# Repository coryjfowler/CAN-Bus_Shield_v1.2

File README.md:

CAN-Bus_Shield_v1.2
====================

I updated the schematic to migrate the SPI connections over to the ICSP header to allow the Shield to be compatible with other Arduinos that do not use digital pins 11-13 for SPI.  I also provided the option to select /INT pin.

This version is capable of operating at 3.3V BUT the MCP2562 still needs +5V to operate the CAN bus.  There is a solder-jumper pad to select the voltage of operation if IOREF pin is not used.

This version has two pinouts on the DE9 for CAN.  These two pinouts are not enabled by default, there are three solder-jumpers on the bottom of the PCB.  The dots indicate the "Standard CAN Pinout" commonly used and the opposite retains compatibility with the OBDII cable which started this whole mess.

This version features a split termination that is not enabled by default.  The split termination improves CMRR.

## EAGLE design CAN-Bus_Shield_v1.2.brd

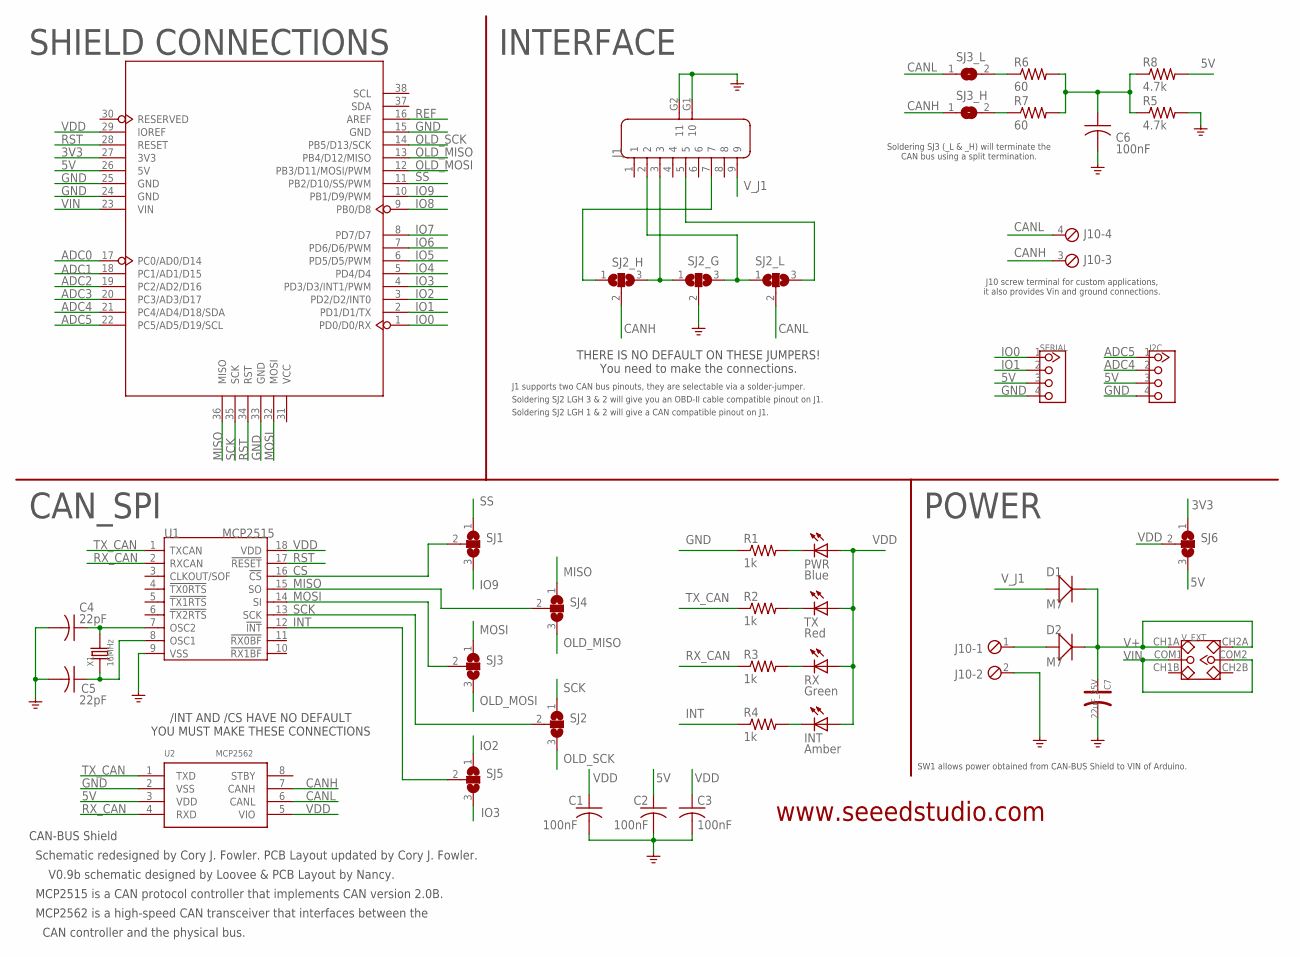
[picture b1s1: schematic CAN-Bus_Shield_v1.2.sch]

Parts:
C1, C2, C3: 100nF; C0603K
C4, C5: 22pF; C0603
C6: 100nF; C1210
C7: 22uF_25V; AVX-C
D1, D2: M7; D2010
I2C: TWIG-4P-2.0-2.0; 4P-2.0
INT: Amber; CHIP-LED0805
J1: DB9'MEAL'; DB9-MEAL
J10: MPT4; 4POL254
PWR: Blue; CHIP-LED0805
R1, R2, R3, R4: 1k; M0805
R5, R8: 4.7k; M3216
R6, R7: 60; M3216
RX: Green; CHIP-LED0805
SERIAL: TWIG-4P-2.0-2.0; 4P-2.0
SJ1, SJ2, SJ2_G, SJ2_H, SJ2_L, SJ3, SJ4, SJ5, SJ6: SJ2W; SJ_2
SJ3_H, SJ3_L: SJ
TX: Red; CHIP-LED0805
U1: MCP2515; SOIC18
U2: MCP2562; SO08
U3: ARDUINO
V_EXT: SWITCH-2CH-6P; 6P-2CH-2.54-7.6X3.0
X1: 16MHz; HC49/S

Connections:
3V3: SJ6.1, U3.27 (3V3)
5V: C2.1, I2C.3, R8.2, SERIAL.3, SJ6.3, U2.3 (VDD), U3.26 (5V)
ADC0: U3.17 (PC0/AD0/D14)
ADC1: U3.18 (PC1/AD1/D15)
ADC2: U3.19 (PC2/AD2/D16)
ADC3: U3.20 (PC3/AD3/D17)
ADC4: I2C.2, U3.21 (PC4/AD4/D18/SDA)
ADC5: I2C.1, U3.22 (PC5/AD5/D19/SCL)
CANH: J10.3, SJ2_H.2, SJ3_H.1, U2.7 (CANH)
CANL: J10.4, SJ2_L.2, SJ3_L.1, U2.6 (CANL)
CS: SJ1.2, U1.16 (!CS)
GND: C1.2, C2.2, C3.2, C4.2, C5.2, C6.2, C7.-, I2C.4, J1.G1 (10), J1.G2 (11), J10.2, R1.1, R5.2, SERIAL.4, SJ2_G.2, U1.9 (VSS), U2.2 (VSS), U3.15 (GND), U3.24 (GND), U3.25 (GND), U3.33 (GND)
INT: R4.1, SJ5.2, U1.12 (!INT)
IO0: SERIAL.1, U3.1 (PD0/D0/RX)
IO1: SERIAL.2, U3.2 (PD1/D1/TX)
IO2: SJ5.1, U3.3 (PD2/D2/INT0)
IO3: SJ5.3, U3.4 (PD3/D3/INT1/PWM)
IO4: U3.5 (PD4/D4)
IO5: U3.6 (PD5/D5/PWM)
IO6: U3.7 (PD6/D6/PWM)
IO7: U3.8 (PD7/D7)
IO8: U3.9 (PB0/D8)
IO9: SJ1.3, U3.10 (PB1/D9/PWM)
MISO: SJ4.1, SJ4.2, U1.15 (SO), U3.36 (MISO)
MOSI: SJ3.1, SJ3.2, U1.14 (SI), U3.32 (MOSI)
unnamed: PWR.C, R1.2
unnamed: R2.2, TX.C
unnamed: R3.2, RX.C
unnamed: J1.2, SJ2_G.3, SJ2_L.1
unnamed: J1.7, SJ2_H.1
unnamed: J1.3, SJ2_G.1, SJ2_H.3
unnamed: R6.1, SJ3_L.2
unnamed: R7.1, SJ3_H.2
unnamed: C6.1, R5.1, R6.2, R7.2, R8.1
unnamed: C5.1, U1.8 (OSC1), X1.1
unnamed: C4.1, U1.7 (OSC2), X1.2
unnamed: INT.C, R4.2
unnamed: J1.5, SJ2_L.3
OLD_MISO: SJ4.3, U3.13 (PB4/D12/MISO)
OLD_MOSI: SJ3.3, U3.12 (PB3/D11/MOSI/PWM)
OLD_SCK: SJ2.3, U3.14 (PB5/D13/SCK)
REF: U3.16 (AREF)
RST: U1.17 (!RESET), U3.28 (RESET), U3.34 (RST)
RX_CAN: R3.1, U1.2 (RXCAN), U2.4 (RXD)
SCK: SJ2.1, SJ2.2, U1.13 (SCK), U3.35 (SCK)
SS: SJ1.1, U3.11 (PB2/D10/SS/PWM)
TX_CAN: R2.1, U1.1 (TXCAN), U2.1 (TXD)
V+: C7.+, D1.-, D2.-, V_EXT.CH1A, V_EXT.CH2A
VDD: C1.1, C3.1, INT.A, PWR.A, RX.A, SJ6.2, TX.A, U1.18 (VDD), U2.5 (VIO), U3.29 (IOREF)
VIN: U3.23 (VIN), V_EXT.COM1, V_EXT.COM2
V_J1: D1.+, J1.9
V_J10: D2.+, J10.1

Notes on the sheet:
CAN_SPI
SHIELD CONNECTIONS
INTERFACE
POWER
CAN-BUS Shield
V0.9b schematic designed by Loovee & PCB Layout by Nancy.
Schematic redesigned by Cory J. Fowler. PCB Layout updated by Cory J. Fowler.
MCP2562 is a high-speed CAN transceiver that interfaces between the
CAN controller and the physical bus.
MCP2515 is a CAN protocol controller that implements CAN version 2.0B.
www.seeedstudio.com
SW1 allows power obtained from CAN-BUS Shield to VIN of Arduino.
J1 supports two CAN bus pinouts, they are selectable via a solder-jumper.
J10 screw terminal for custom applications, it also provides Vin and ground connections.
Soldering SJ2 LGH 3 & 2 will give you an OBD-II cable compatible pinout on J1.
Soldering SJ2 LGH 1 & 2 will give a CAN compatible pinout on J1.
Soldering SJ3 (_L & _H) will terminate the CAN bus using a split termination.
THERE IS NO DEFAULT ON THESE JUMPERS! You need to make the connections.
/INT AND /CS HAVE NO DEFAULT YOU MUST MAKE THESE CONNECTIONS

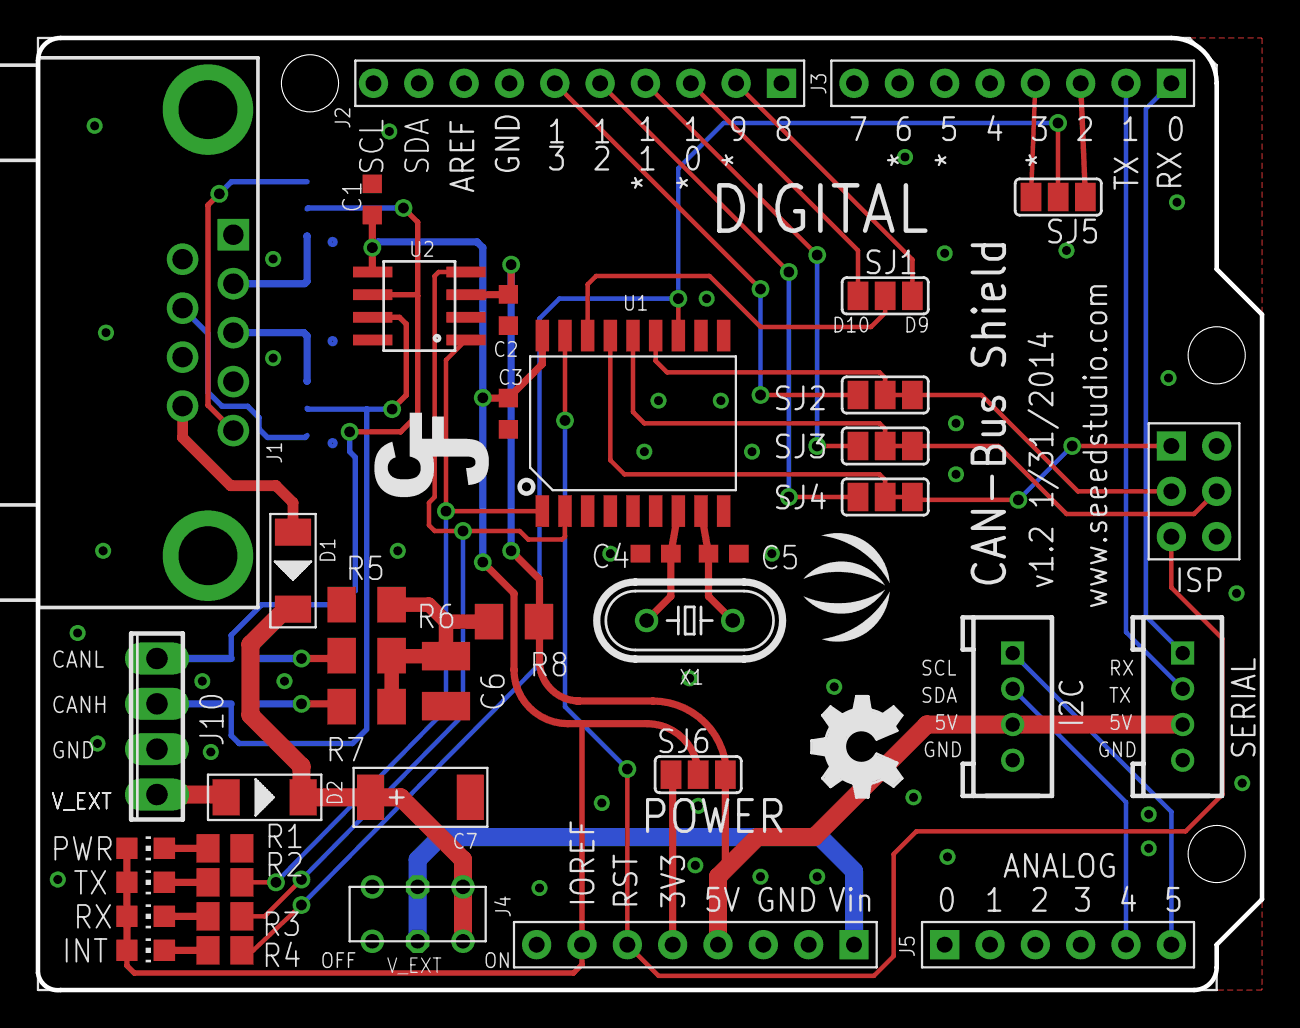
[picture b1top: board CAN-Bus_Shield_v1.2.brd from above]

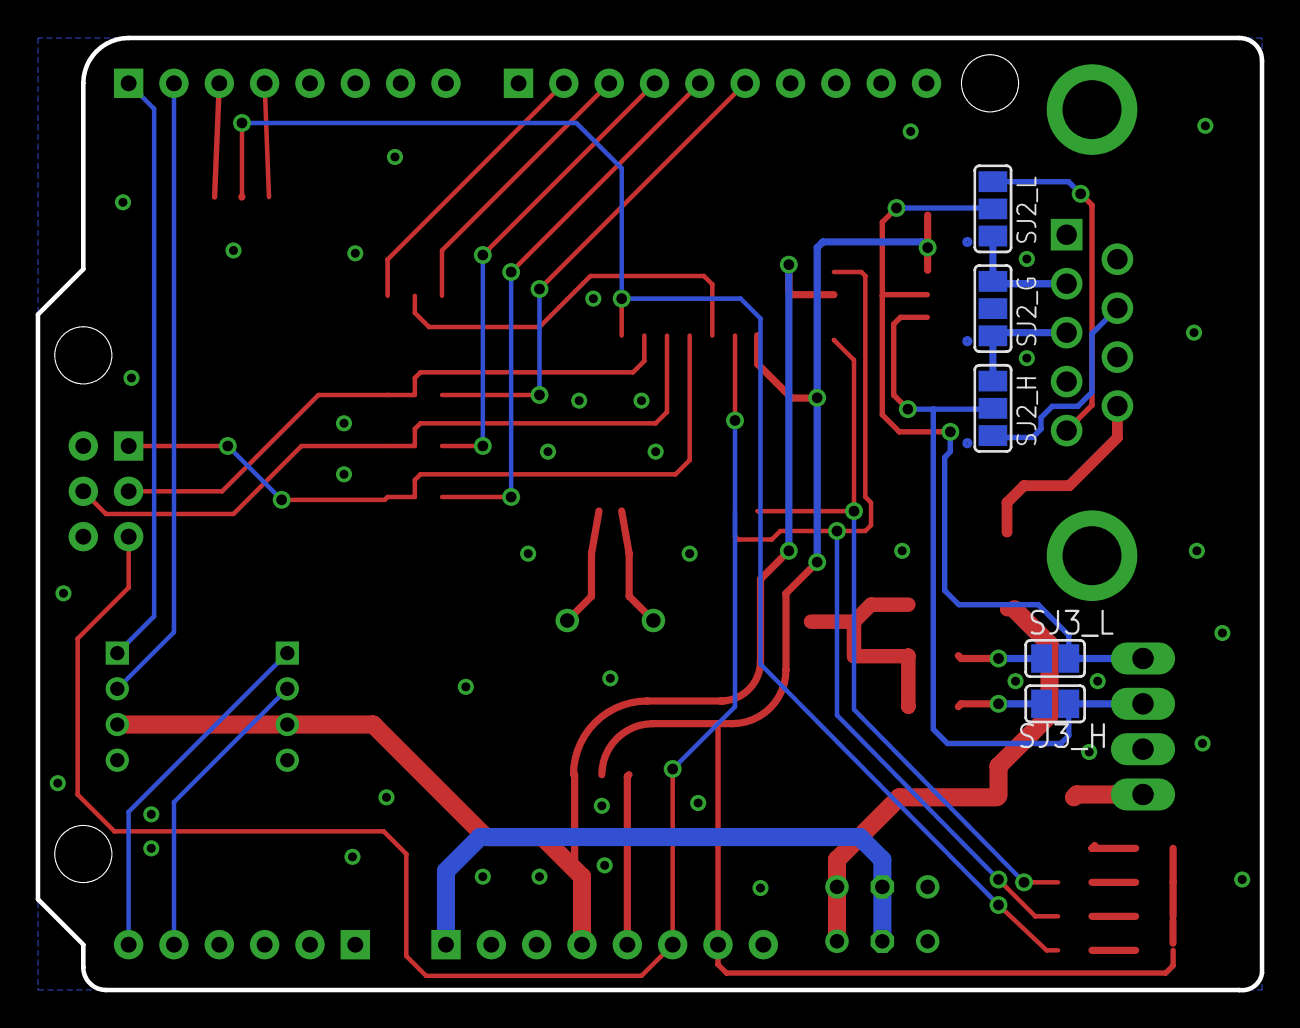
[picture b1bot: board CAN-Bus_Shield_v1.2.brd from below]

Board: 2 copper layers, 68.6 x 53.4 mm, 44 parts (5 on the bottom side), 42 nets.

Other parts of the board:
U$1: LOGO_SILK
U$2: OSHW_FILLX200_NOTEXT
U$9: CJF
